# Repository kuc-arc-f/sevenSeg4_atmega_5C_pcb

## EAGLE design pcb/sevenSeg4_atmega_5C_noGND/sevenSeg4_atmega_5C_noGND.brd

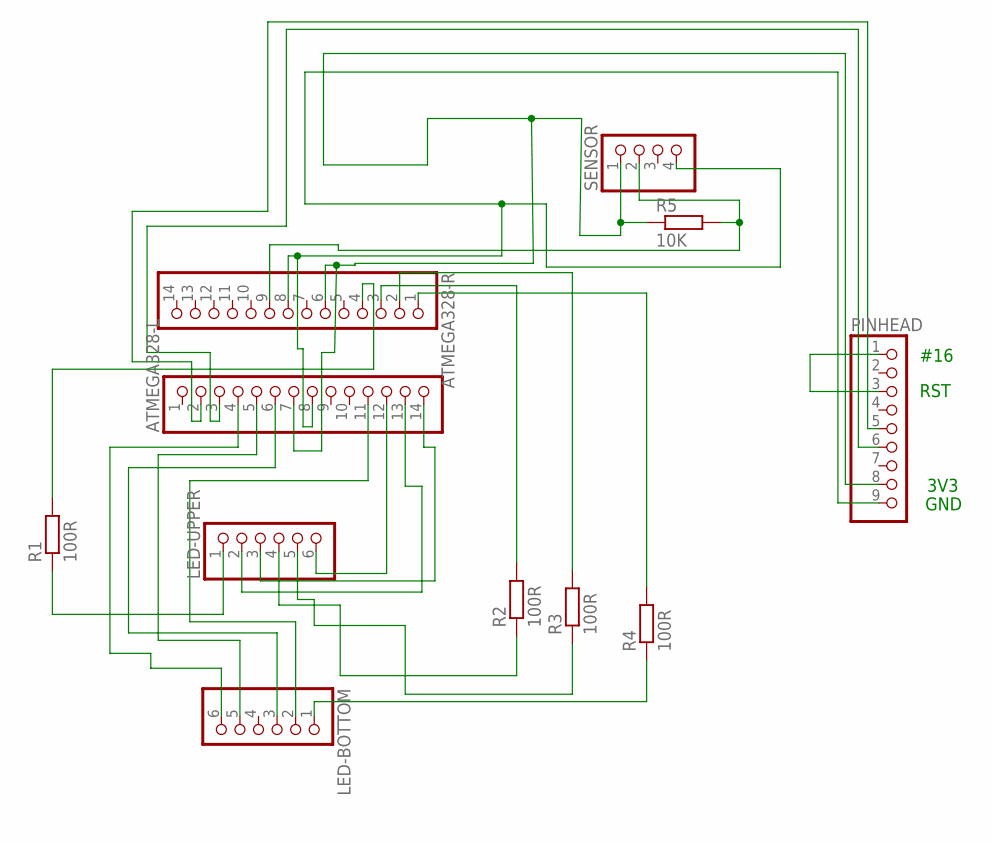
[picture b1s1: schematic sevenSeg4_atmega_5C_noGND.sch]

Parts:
ATMEGA328-L, ATMEGA328-R: PINHD-1X14; 1X14
LED-BOTTOM: PINHD-1X6; 1X06
LED-UPPER: PINHD-1X6; 1X06
PINHEAD: PINHD-1X9; 1X09
R1, R2, R3, R4: 100R; R0603
R5: 10K; R0603
SENSOR: PINHD-1X4; 1X04

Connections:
unnamed: ATMEGA328-L.7, ATMEGA328-R.6, PINHEAD.8, R5.1, SENSOR.1
unnamed: ATMEGA328-R.9, R5.2, SENSOR.2
unnamed: ATMEGA328-L.3, PINHEAD.6
unnamed: PINHEAD.1, PINHEAD.3
unnamed: ATMEGA328-L.4, LED-BOTTOM.6
unnamed: ATMEGA328-L.5, LED-BOTTOM.5
unnamed: ATMEGA328-L.6, LED-BOTTOM.3
unnamed: ATMEGA328-L.11, LED-BOTTOM.2
unnamed: LED-UPPER.1, R1.1
unnamed: ATMEGA328-L.12, LED-UPPER.6
unnamed: ATMEGA328-R.3, R2.2
unnamed: LED-UPPER.4, R2.1
unnamed: ATMEGA328-L.13, LED-UPPER.2
unnamed: ATMEGA328-L.14, LED-UPPER.3
unnamed: ATMEGA328-R.4, R1.2
unnamed: ATMEGA328-R.2, R3.2
unnamed: LED-UPPER.5, R3.1
unnamed: ATMEGA328-R.1, R4.2
unnamed: LED-BOTTOM.1, R4.1
unnamed: ATMEGA328-L.8, ATMEGA328-R.8, PINHEAD.9, SENSOR.4
unnamed: ATMEGA328-L.2, PINHEAD.5

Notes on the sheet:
GND
3V3
RST
#16

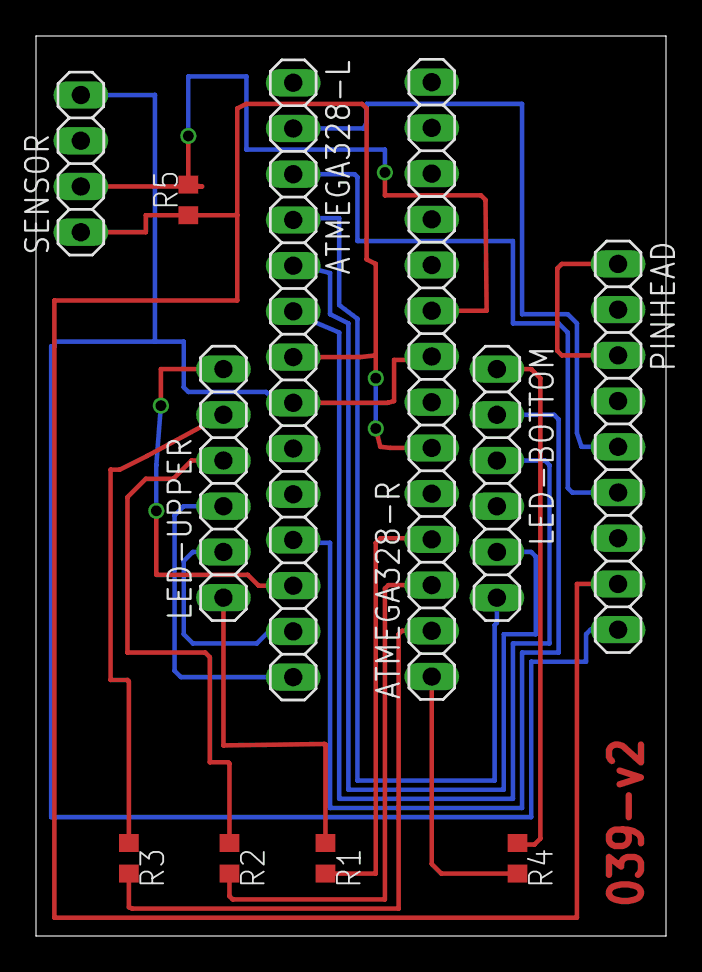
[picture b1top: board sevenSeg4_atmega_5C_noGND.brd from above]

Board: 2 copper layers, 35.0 x 50.0 mm, 11 parts (0 on the bottom side), 21 nets.

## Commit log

2016-10-29 new, 10-29A1
2017-08-17 up, 08-17a1
